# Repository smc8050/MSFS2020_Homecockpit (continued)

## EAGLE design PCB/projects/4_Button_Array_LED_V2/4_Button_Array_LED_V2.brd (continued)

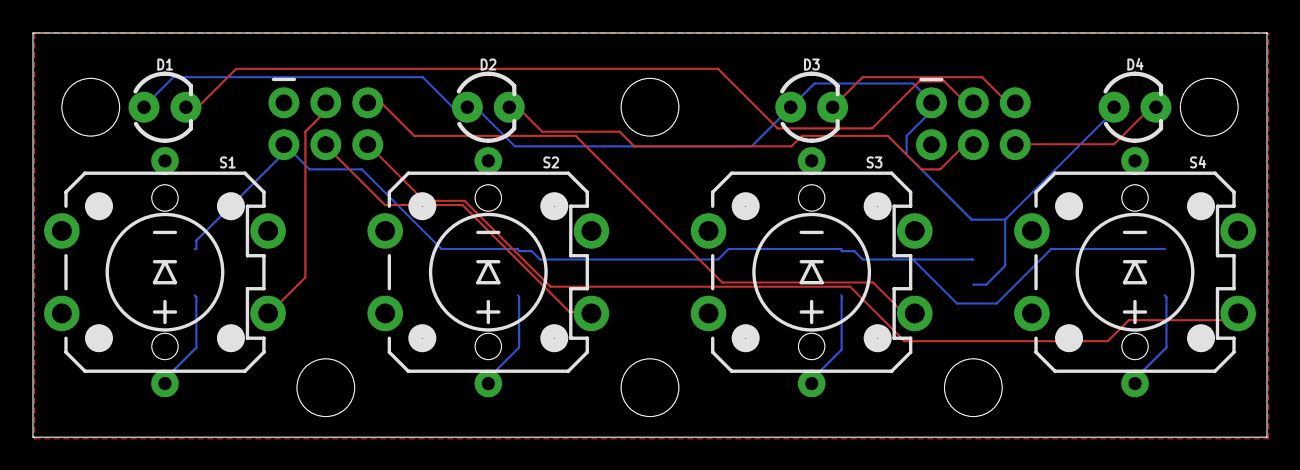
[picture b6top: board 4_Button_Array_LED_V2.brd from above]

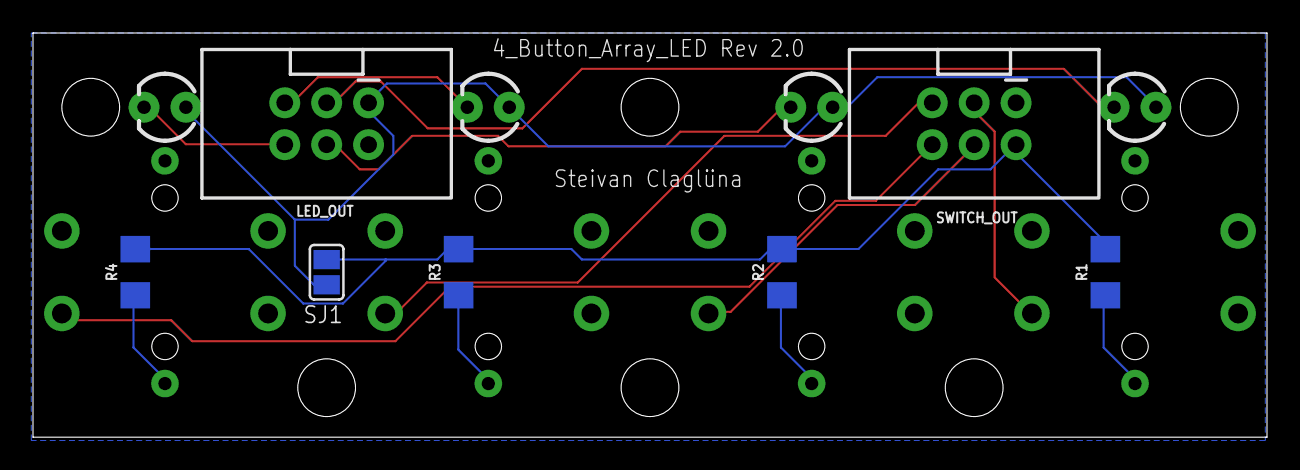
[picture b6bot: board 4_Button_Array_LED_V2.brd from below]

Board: 2 copper layers, 74.8 x 24.5 mm, 15 parts (7 on the bottom side), 15 nets.

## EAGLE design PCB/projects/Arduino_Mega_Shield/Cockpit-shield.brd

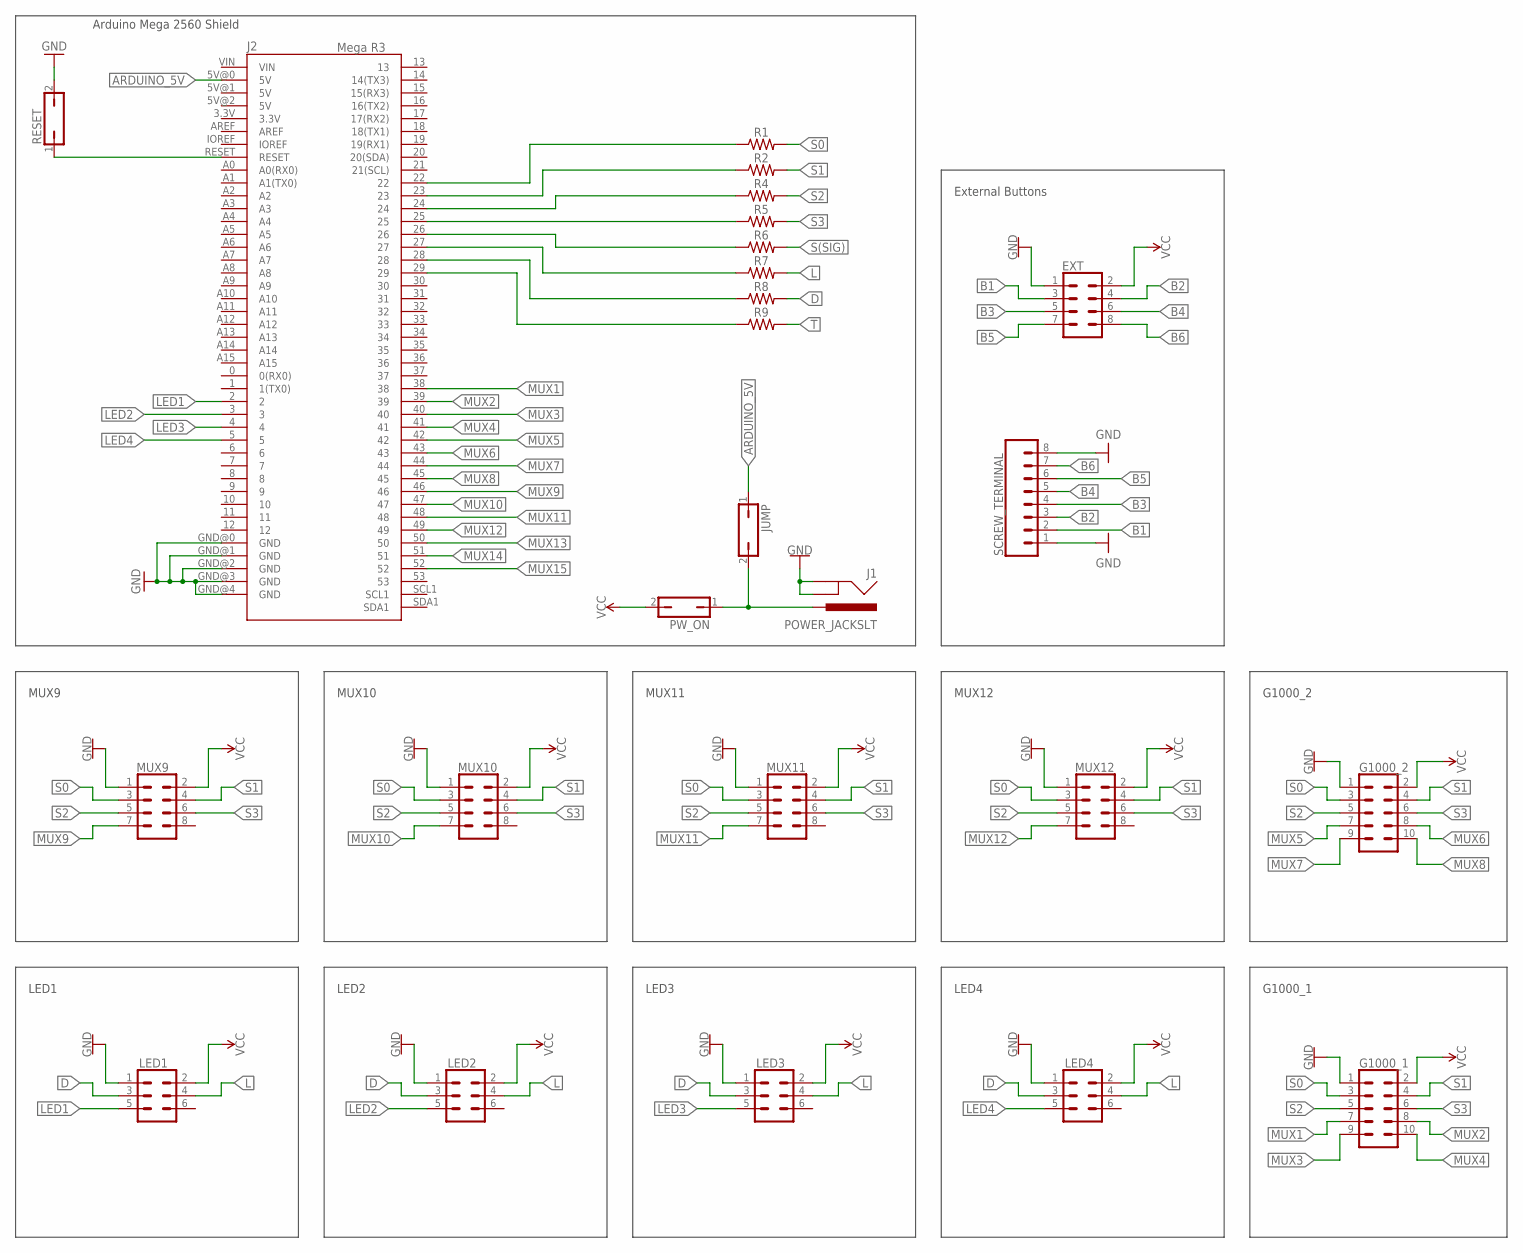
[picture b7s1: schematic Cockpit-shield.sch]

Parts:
EXT: CONN_04X2; 2X4
G1000_1, G1000_2: CONN_05X2SHD-NS; 2X5-SHROUDED-NS
J1: POWER_JACKSLT; POWER_JACK_SLOT
J2: Mega R3; ARDUINO_MEGA
JUMP: JP1Q; JP1
LED1, LED2, LED3, LED4: CONN_03X2NO_SILK; 2X3-NS
MUX9, MUX10, MUX11, MUX12: CONN_04X2; 2X4
PW_ON: JP1Q; JP1
R1, R2, R4, R5, R6, R7, R8, R9: 1206
RESET: JP1Q; JP1
SCREW_TERMINAL: CONN_083.5MM-8; SCREWTERMINAL-3.5MM-8

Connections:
ARDUINO_5V: J2.5V@0 (5V), JUMP.1
B1: EXT.3, SCREW_TERMINAL.2
B2: EXT.4, SCREW_TERMINAL.3
B3: EXT.5, SCREW_TERMINAL.4
B4: EXT.6, SCREW_TERMINAL.5
B5: EXT.7, SCREW_TERMINAL.6
B6: EXT.8, SCREW_TERMINAL.7
D: LED1.3, LED2.3, LED3.3, LED4.3, R8.2
GND: EXT.1, G1000_1.1, G1000_2.1, J1.GND@1 (GNDBREAK), J1.GND@2 (GND), J2.GND@0 (GND), J2.GND@1 (GND), J2.GND@2 (GND), J2.GND@3 (GND), J2.GND@4 (GND), LED1.1, LED2.1, LED3.1, LED4.1, MUX9.1, MUX10.1, MUX11.1, MUX12.1, RESET.2, SCREW_TERMINAL.1, SCREW_TERMINAL.8
L: LED1.4, LED2.4, LED3.4, LED4.4, R7.2
LED1: J2.2, LED1.5
LED2: J2.3, LED2.5
LED3: J2.4, LED3.5
LED4: J2.5, LED4.5
MUX1: G1000_1.7, J2.38
MUX2: G1000_1.8, J2.39
MUX3: G1000_1.9, J2.40
MUX4: G1000_1.10, J2.41
MUX5: G1000_2.7, J2.42
MUX6: G1000_2.8, J2.43
MUX7: G1000_2.9, J2.44
MUX8: G1000_2.10, J2.45
MUX9: J2.46, MUX9.7
MUX10: J2.47, MUX10.7
MUX11: J2.48, MUX11.7
MUX12: J2.49, MUX12.7
MUX13: J2.50
MUX14: J2.51
MUX15: J2.52
unnamed: J2.22, R1.1
unnamed: J2.23, R2.1
unnamed: J2.24, R4.1
unnamed: J2.25, R5.1
unnamed: J2.26, R6.1
unnamed: J2.27, R7.1
unnamed: J2.28, R8.1
unnamed: J2.29, R9.1
unnamed: J1.PWR, JUMP.2, PW_ON.1
RESET: J2.RESET, RESET.1
S0: G1000_1.3, G1000_2.3, MUX9.3, MUX10.3, MUX11.3, MUX12.3, R1.2
S1: G1000_1.4, G1000_2.4, MUX9.4, MUX10.4, MUX11.4, MUX12.4, R2.2
S2: G1000_1.5, G1000_2.5, MUX9.5, MUX10.5, MUX11.5, MUX12.5, R4.2
S3: G1000_1.6, G1000_2.6, MUX9.6, MUX10.6, MUX11.6, MUX12.6, R5.2
S(SIG): R6.2
T: R9.2
VCC: EXT.2, G1000_1.2, G1000_2.2, LED1.2, LED2.2, LED3.2, LED4.2, MUX9.2, MUX10.2, MUX11.2, MUX12.2, PW_ON.2

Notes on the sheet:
Arduino Mega 2560 Shield
G1000_1
G1000_2
MUX9
MUX10
MUX11
MUX12
LED1
LED2
LED3
LED4
External Buttons

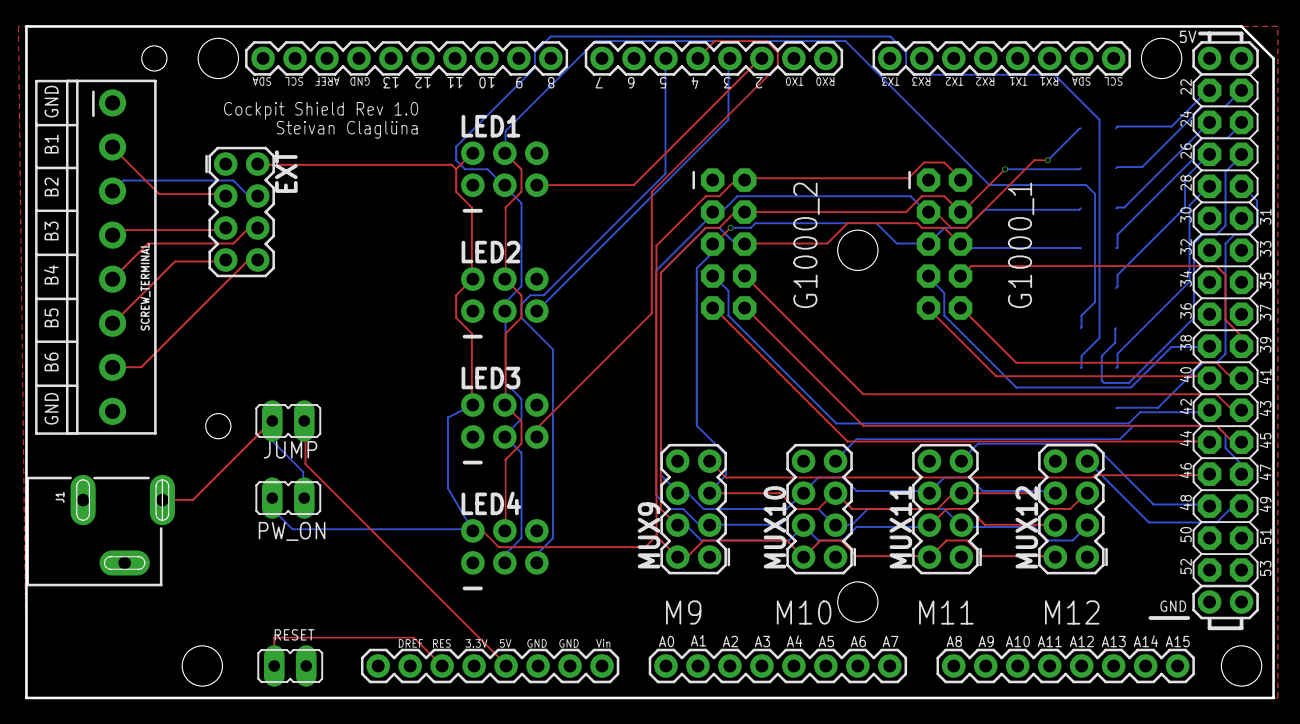
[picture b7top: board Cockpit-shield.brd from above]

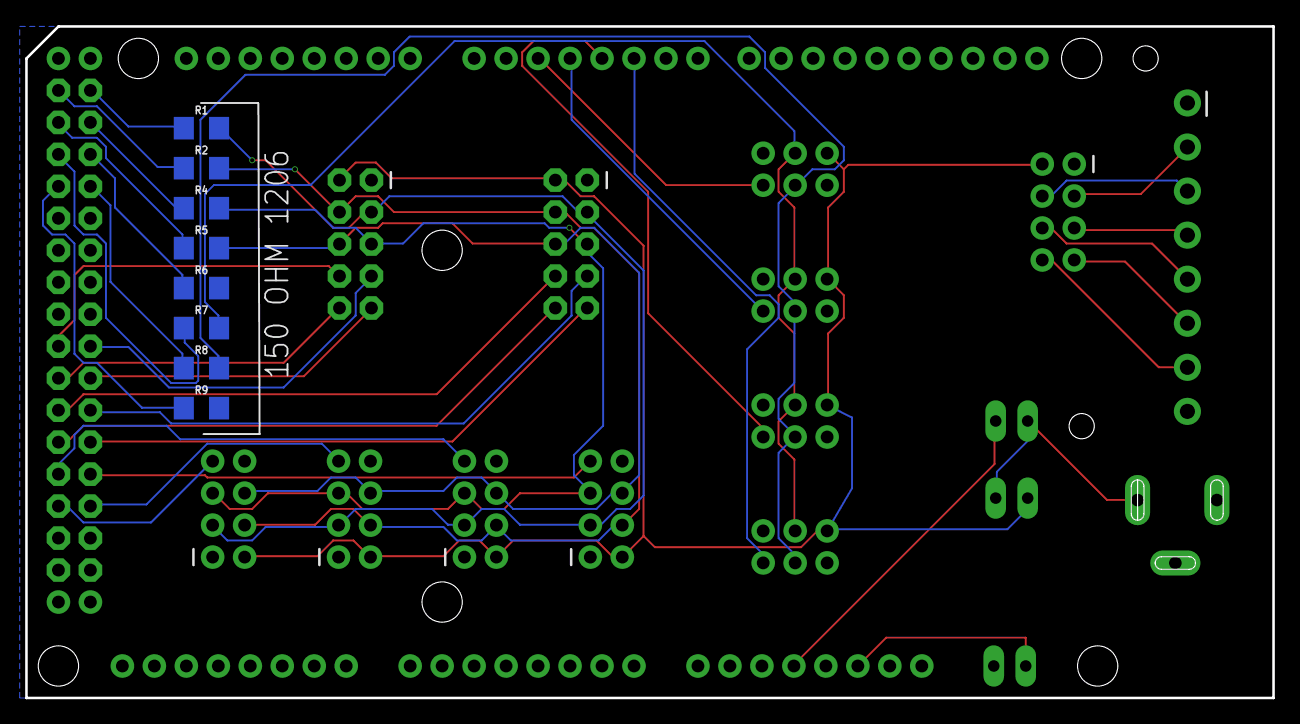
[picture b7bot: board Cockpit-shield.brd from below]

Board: 2 copper layers, 99.1 x 53.3 mm, 25 parts (8 on the bottom side), 41 nets.

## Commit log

2021-01-19 Add files via upload
    These Icons are taken from the Open Icon library
2021-01-19 Create LICENSE
2021-01-24 push testing
2021-01-24 reading window coordinates from json file
2021-01-24 Backlink to CADLAB.io has been added.
2021-01-24 Initial upload of PCB files
    Initial upload of all PCB, libraries and ulp's for EAGLE CAD
2021-01-24 Rename CAD_files.md to CAD_README.md
2021-01-24 Rename PCB_README.md to README.md
2021-01-24 Rename CAD_README.md to README.md
2021-02-19 Added multiplexed encoders support
2021-02-19 Added encoders_commands
2021-02-19 Created script to write all settings files
2021-02-19 smaller bugfixes
2021-02-25 added Relais functionality
2021-02-25 added multiplexed encoder library
2021-02-25 replaced Excel file with CSV file for configuration
2021-02-25 Delete MUX_Pinout.xlsm
    replaced with CSV file in the Python folder
2021-02-25 Delete encodersetup.h
    integrated to cockpit_io.h
2021-02-25 add cockpit_config.json
2021-02-25 minor fixes
